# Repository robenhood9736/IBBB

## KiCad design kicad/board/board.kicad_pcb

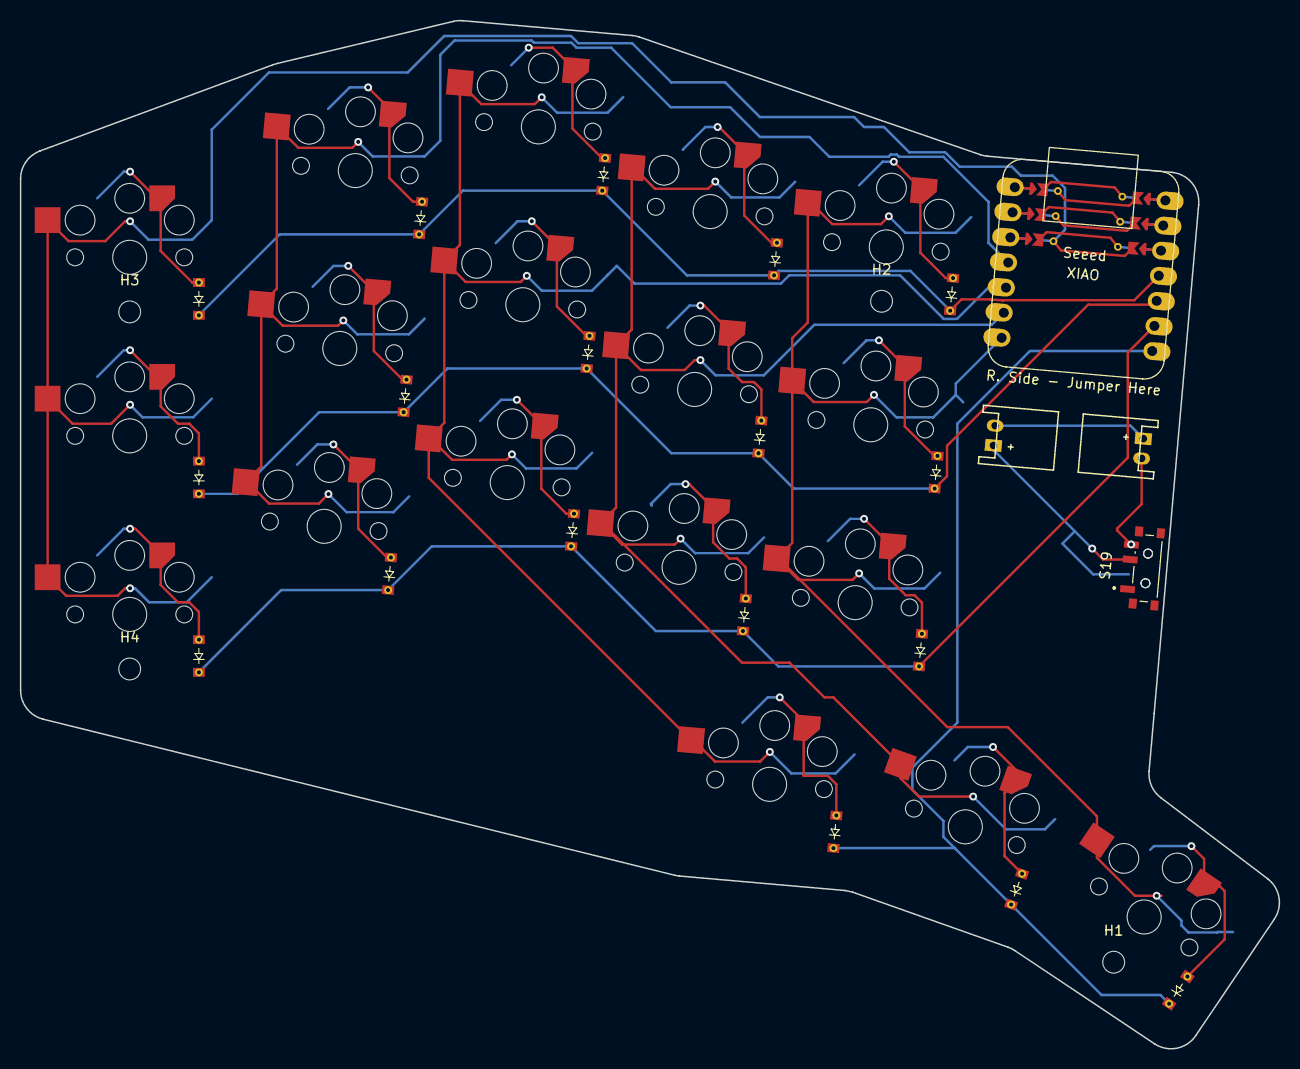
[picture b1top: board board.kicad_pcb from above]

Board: 2 copper layers, 126.9 x 103.7 mm, 45 parts (1 on the bottom side), 30 nets.

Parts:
D1, D2, D3, D4, D5, D6, D7, D8, D9, D10, D11, D12, D13, D14, D15, D16, D17, D18: D; reversable_diode
H1, H2, H3, H4: MountingHole; MountingHole_2.2mm_M2
JST1, JST2: Conn_01x02; JST_angled
S1, S2, S3, S4, S5, S6, S7, S8, S9, S10, S11, S12, S13, S14, S15, S16, S17, S18: SW_SPST; choc_switches
S19, S20: SSSS811101; SW_SSSS811101
U1: seeed_xaio

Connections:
C0: S1.2 (B), S2.2 (B), S3.2 (B), U1.2
C1: S4.2 (B), S5.2 (B), S6.2 (B), U1.3
C2: S7.2 (B), S8.2 (B), S9.2 (B), S16.2 (B), U1.4
C3: S10.2 (B), S11.2 (B), S12.2 (B), S17.2 (B), U1.5
C4: S13.2 (B), S14.2 (B), S15.2 (B), S18.2 (B), U1.6
G0: D3.1 (K), D6.1 (K), D9.1 (K), D12.1 (K), D15.1 (K), U1.10
G1: D2.1 (K), D5.1 (K), D8.1 (K), D11.1 (K), D14.1 (K), U1.9
G2: D1.1 (K), D4.1 (K), D7.1 (K), D10.1 (K), D13.1 (K), U1.8
G3: D16.1 (K), D17.1 (K), D18.1 (K), U1.7
unnamed: D1.2 (A), S1.1 (A)
unnamed: D2.2 (A), S2.1 (A)
unnamed: D3.2 (A), S3.1 (A)
unnamed: D4.2 (A), S4.1 (A)
unnamed: D5.2 (A), S5.1 (A)
unnamed: D6.2 (A), S6.1 (A)
unnamed: D7.2 (A), S7.1 (A)
unnamed: D8.2 (A), S8.1 (A)
unnamed: D9.2 (A), S9.1 (A)
unnamed: D10.2 (A), S10.1 (A)
unnamed: D11.2 (A), S11.1 (A)
unnamed: D12.2 (A), S12.1 (A)
unnamed: D13.2 (A), S13.1 (A)
unnamed: D14.2 (A), S14.1 (A)
unnamed: D15.2 (A), S15.1 (A)
unnamed: D16.2 (A), S16.1 (A)
unnamed: D17.2 (A), S17.1 (A)
unnamed: D18.2 (A), S18.1 (A)
unnamed: JST1.1, S19.2, S20.2
unnamed: JST1.2, JST2.1
unnamed: JST2.2, S19.3, S20.1

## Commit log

2024-11-14 added mounting holes
2024-11-14 added diodes
2024-11-14 wired up and imported
2024-11-14 fixed footprints
2024-11-21 we messed up pcb
2024-11-21 traces
